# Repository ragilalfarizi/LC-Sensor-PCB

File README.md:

# LC Sensor PCB
 Designed during internship program in Badan Riset dan Inovasi Nasional (BRIN)

 ---

 ## Schematic

 ## PCB Layout

 ## 3D View

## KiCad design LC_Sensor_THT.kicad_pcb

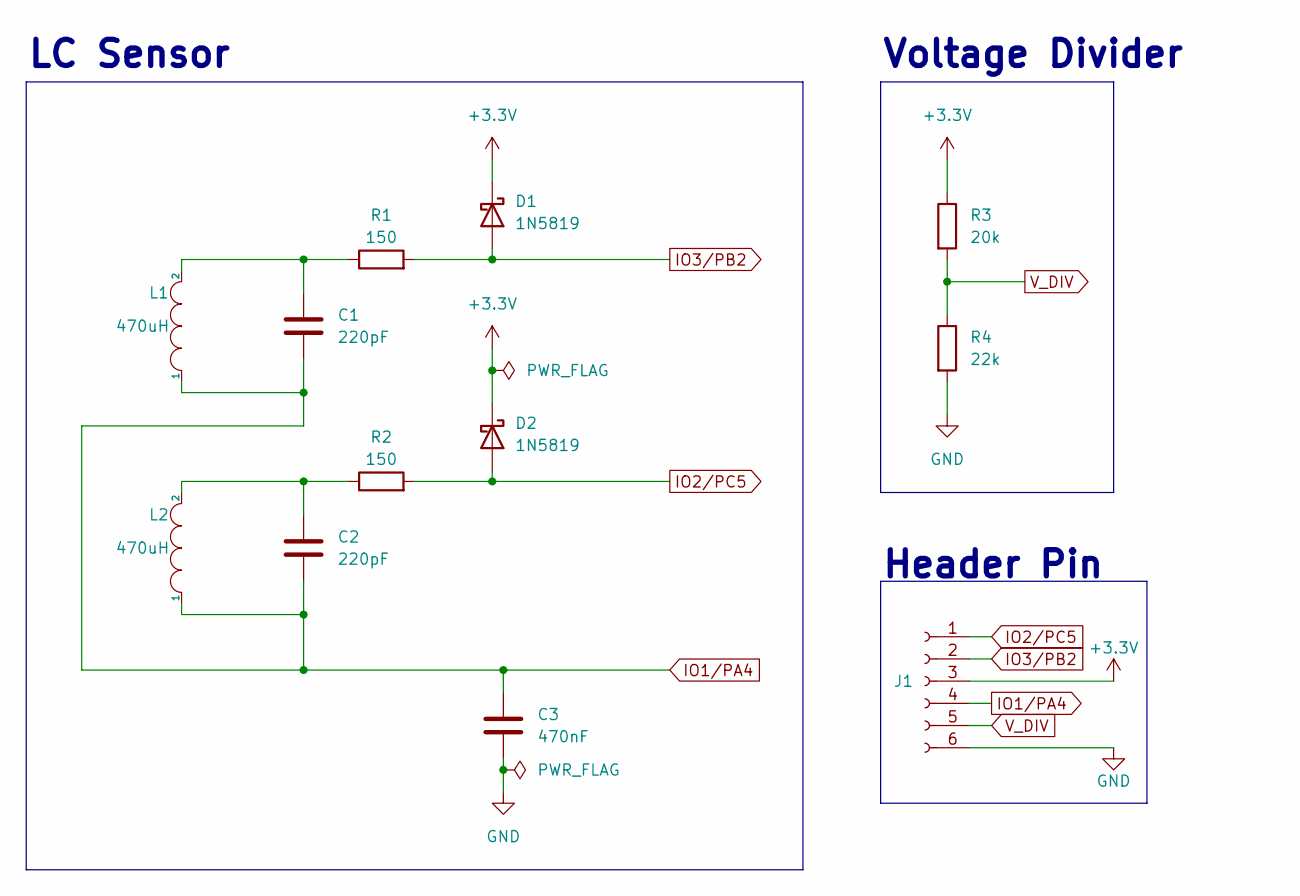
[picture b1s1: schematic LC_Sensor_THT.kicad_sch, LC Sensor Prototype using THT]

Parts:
C1, C2: 220pF; C_Rect_L7.0mm_W2.0mm_P5.00mm
C3: 470nF; C_Rect_L7.0mm_W2.0mm_P5.00mm
D1, D2: 1N5819; D_DO-41_SOD81_P10.16mm_Horizontal
J1: Conn_01x06_Female; PinSocket_1x06_P2.54mm_Vertical
L1, L2: 470uH; L_Radial_D7.2mm_P3.00mm_Murata_1700
R1, R2: 150; R_Axial_DIN0207_L6.3mm_D2.5mm_P10.16mm_Horizontal
R3: 20k; R_Axial_DIN0207_L6.3mm_D2.5mm_P10.16mm_Horizontal
R4: 22k; R_Axial_DIN0207_L6.3mm_D2.5mm_P10.16mm_Horizontal

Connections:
+3.3V: D1.1 (K), D2.1 (K), J1.3, R3.1
GND: C3.2, J1.6, R4.2
IO1/PA4: C1.2, C2.2, C3.1, J1.4, L1.1, L2.1
IO2/PC5: D2.2 (A), J1.1, R2.2
IO3/PB2: D1.2 (A), J1.2, R1.2
unnamed: C1.1, L1.2, R1.1
unnamed: C2.1, L2.2, R2.1
V_DIV: J1.5, R3.2, R4.1

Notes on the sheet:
Voltage Divider
LC Sensor
Header Pin

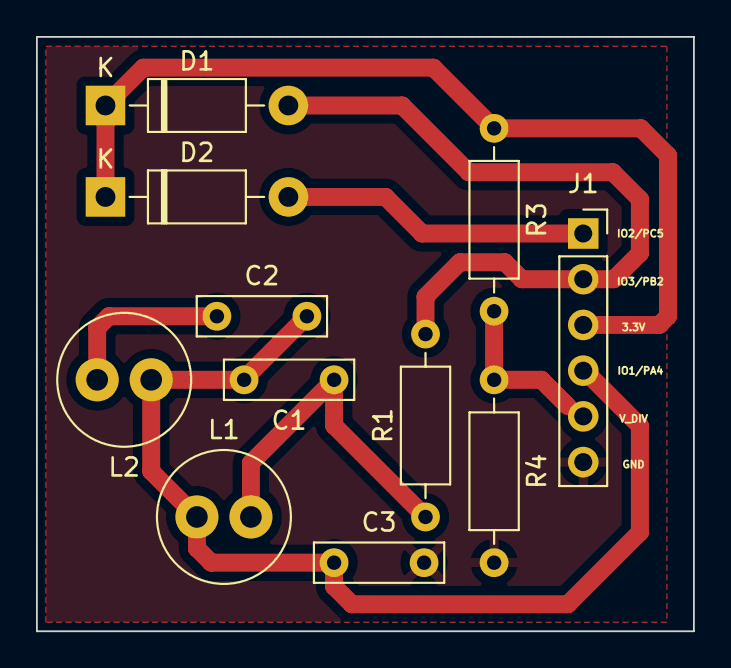
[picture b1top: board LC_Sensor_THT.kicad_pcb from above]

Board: 2 copper layers, 36.5 x 33.0 mm, 11 parts (0 on the bottom side), 8 nets.

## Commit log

2023-06-24 feat: add README.md content
2023-06-24 fix: broken link to images
